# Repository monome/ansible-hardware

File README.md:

# ansible hardware

eurorack module by https://monome.org

created by brian crabtree (bcrabtree@monome.org)

all circuits in eagle. can be imported to kicad.

firmware: https://github.com/monome/ansible

## notes

"ansible" is the top board, "runes" is the bottom board

## license

[cc-by-sa-3.0](https://creativecommons.org/licenses/by-sa/4.0/)

commerical use: send $10 per unit produced to tehn@nnnnnnnn.co via paypal

do not use the name "monome" or "ansible" in derivative works.

## warranty and support

we can provide neither

## thank you

everyone who helped this module live

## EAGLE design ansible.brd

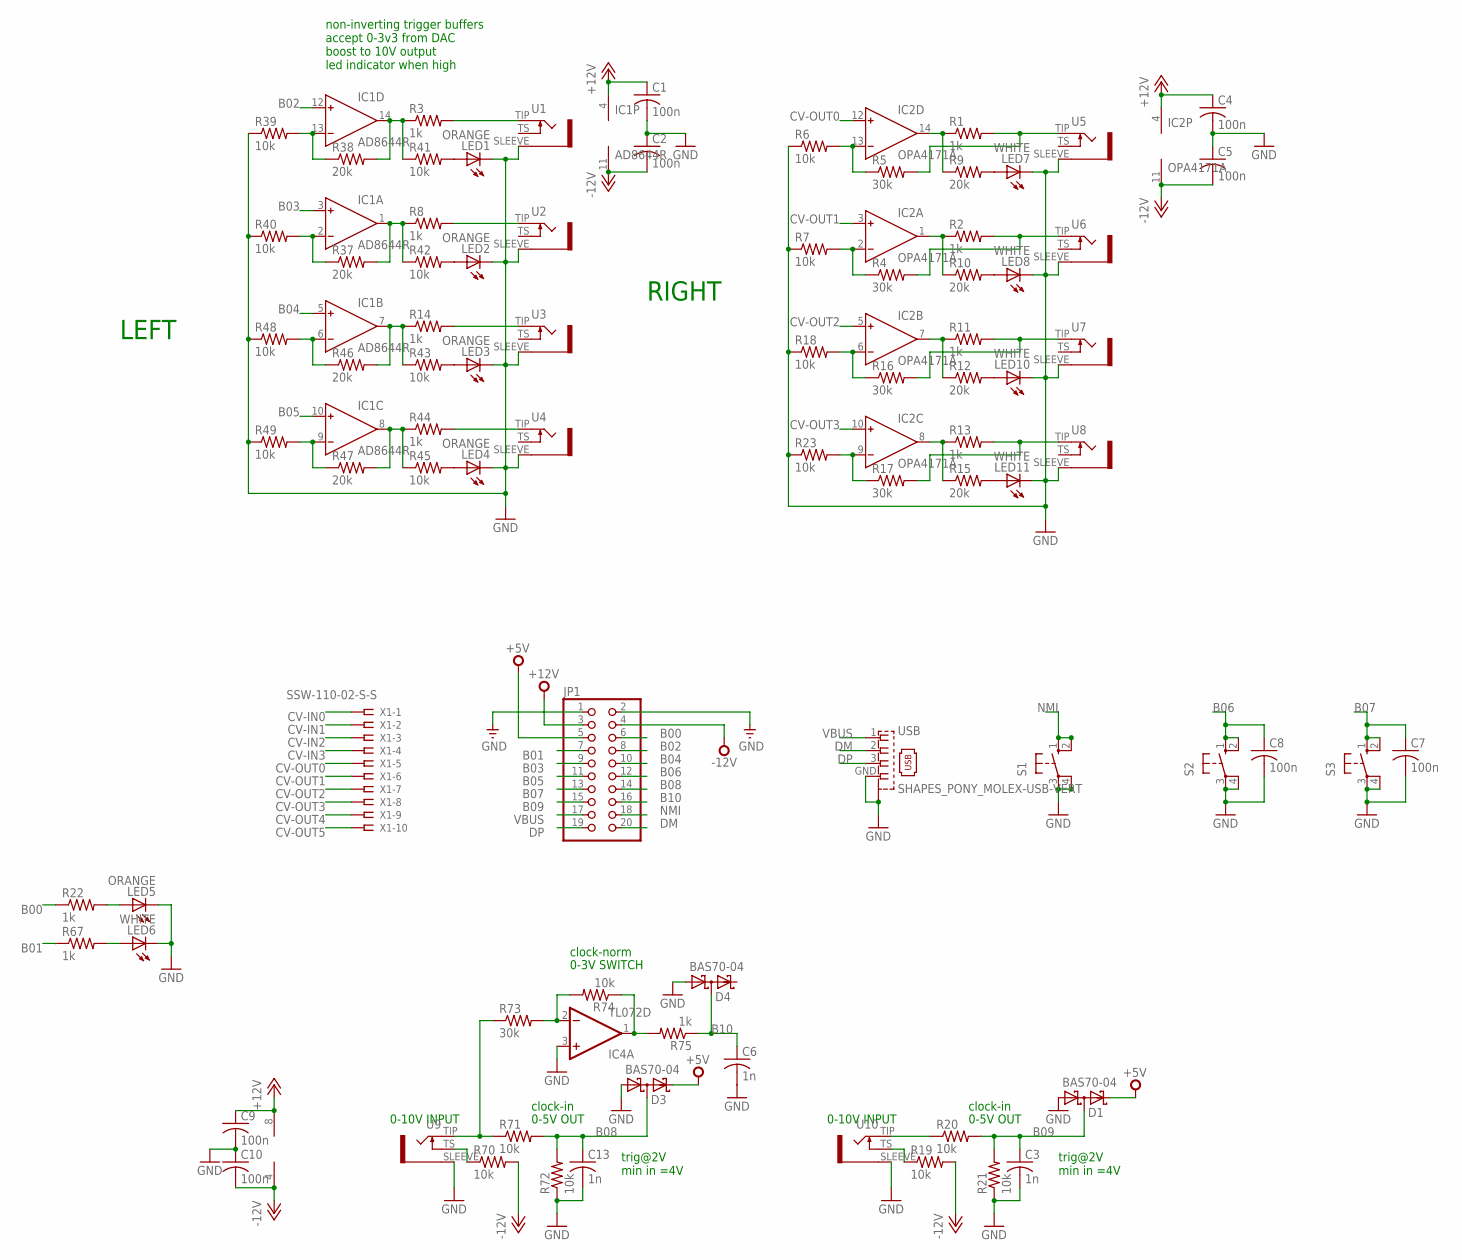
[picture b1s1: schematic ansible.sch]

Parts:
C1, C2, C4, C5, C7, C8, C9, C10: 100n; C0402
C3, C6, C13: 1n; C0402
D1, D3, D4: BAS70-04; SOT23
IC1: AD8644R; SO14
IC2: OPA4171A; SO14
IC4: TL072D; SO08
JP1: PINHD-2X10; 2X10
LED1, LED2, LED3, LED4, LED5: ORANGE; CHIP-LED0603
LED6, LED7, LED8, LED10, LED11: WHITE; CHIP-LED0603
R1, R2, R3, R8, R11, R13, R14, R22, R44, R67, R75: 1k; R0402
R4, R5, R16, R17, R73: 30k; R0402
R6, R7, R18, R19, R20, R21, R23, R39, R40, R41, R42, R43, R45, R48, R49, R70, R71, R72, R74: 10k; R0402
R9, R10, R12, R15, R37, R38, R46, R47: 20k; R0402
S1, S2, S3: 10-XX; B3F-10XX
U1, U2, U3, U4, U5, U6, U7, U8, U9, U10: WQP-PJ301M-12_JACK
USB: SHAPES_PONY_MOLEX-USB-VERT; SHAPES_PONY_MOLEX-USB
X1: SSW-110-02-S-S

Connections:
+5V: D1.2 (C2), D3.2 (C2), JP1.5
+12V: C1.1, C4.1, C9.1, IC1.4 (V+), IC2.4 (V+), IC4.8 (V+), JP1.3
-12V: C2.2, C5.2, C10.2, IC1.11 (V-), IC2.11 (V-), IC4.4 (V-), JP1.4, R19.2, R70.2
B00: JP1.6, R22.1
B01: JP1.7, R67.1
B02: IC1.12 (IN+), JP1.8
B03: IC1.3 (IN+), JP1.9
B04: IC1.5 (IN+), JP1.10
B05: IC1.10 (IN+), JP1.11
B06: C8.1, JP1.12, S2.1 (S), S2.2 (S1)
B07: C7.1, JP1.13, S3.1 (S), S3.2 (S1)
B08: C13.1, D3.3 (C1A2), JP1.14, R71.2, R72.2
B09: C3.1, D1.3 (C1A2), JP1.15, R20.2, R21.2
B10: C6.1, D4.3 (C1A2), JP1.16, R75.1
CV-IN0: X1.1
CV-IN1: X1.2
CV-IN2: X1.3
CV-IN3: X1.4
CV-OUT0: IC2.12 (IN+), X1.5
CV-OUT1: IC2.3 (IN+), X1.6
CV-OUT2: IC2.5 (IN+), X1.7
CV-OUT3: IC2.10 (IN+), X1.8
CV-OUT4: X1.9
CV-OUT5: X1.10
DM: JP1.20, USB.2
DP: JP1.19, USB.3
GND: C1.2, C2.1, C3.2, C4.2, C5.1, C6.2, C7.2, C8.2, C9.2, C10.1, C13.2, D1.1 (A1), D3.1 (A1), D4.1 (A1), IC4.3 (+IN), JP1.1, JP1.2, LED1.C, LED2.C, LED3.C, LED4.C, LED5.C, LED6.C, LED7.C, LED8.C, LED10.C, LED11.C, R6.1, R7.1, R18.1, R21.1, R23.1, R39.1, R40.1, R48.1, R49.1, R72.1, S1.3, S1.4 (P1), S2.3, S2.4 (P1), S3.3, S3.4 (P1), U1.SLEEVE, U2.SLEEVE, U3.SLEEVE, U4.SLEEVE, U5.SLEEVE, U6.SLEEVE, U7.SLEEVE, U8.SLEEVE, U9.SLEEVE, U10.SLEEVE, USB.GND, USB.M1 (S1), USB.M2 (S1), USB.M4 (S1)
N: IC4.1 (OUT), R74.1, R75.2
unnamed: IC4.2 (-IN), R73.2, R74.2
unnamed: IC1.14 (OUT), R3.1, R38.2, R41.1
unnamed: IC1.1 (OUT), R8.1, R37.2, R42.1
unnamed: IC1.7 (OUT), R14.1, R43.1, R46.2
unnamed: IC1.8 (OUT), R44.1, R45.1, R47.2
unnamed: R3.2, U1.TIP
unnamed: R8.2, U2.TIP
unnamed: R14.2, U3.TIP
unnamed: R44.2, U4.TIP
unnamed: R20.1, U10.TIP
unnamed: IC2.14 (OUT), R1.1, R9.1
unnamed: IC2.1 (OUT), R2.1, R10.1
unnamed: IC2.7 (OUT), R11.1, R12.1
unnamed: IC2.8 (OUT), R13.1, R15.1
unnamed: LED5.A, R22.2
unnamed: R13.2, R17.2, U8.TIP
unnamed: IC2.13 (IN-), R5.1, R6.2
unnamed: IC2.2 (IN-), R4.1, R7.2
unnamed: LED7.A, R9.2
unnamed: LED8.A, R10.2
unnamed: R70.1, U9.TS
unnamed: R19.1, U10.TS
unnamed: IC2.9 (IN-), R17.1, R23.2
unnamed: IC2.6 (IN-), R16.1, R18.2
unnamed: LED10.A, R12.2
unnamed: LED11.A, R15.2
unnamed: R1.2, R5.2, U5.TIP
unnamed: R2.2, R4.2, U6.TIP
unnamed: R11.2, R16.2, U7.TIP
unnamed: IC1.9 (IN-), R47.1, R49.2
unnamed: IC1.6 (IN-), R46.1, R48.2
unnamed: R71.1, R73.1, U9.TIP
unnamed: IC1.13 (IN-), R38.1, R39.2
unnamed: IC1.2 (IN-), R37.1, R40.2
unnamed: LED6.A, R67.2
unnamed: LED1.A, R41.2
unnamed: LED2.A, R42.2
unnamed: LED3.A, R43.2
unnamed: LED4.A, R45.2
NMI: JP1.18, S1.1 (S), S1.2 (S1)
VBUS: JP1.17, USB.1

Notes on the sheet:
0-10V INPUT
0-5V OUT
0-3V SWITCH
non-inverting trigger buffers accept 0-3v3 from DAC boost to 10V output led indicator when high
LEFT
RIGHT
clock-norm
clock-in
trig@2V min in =4V

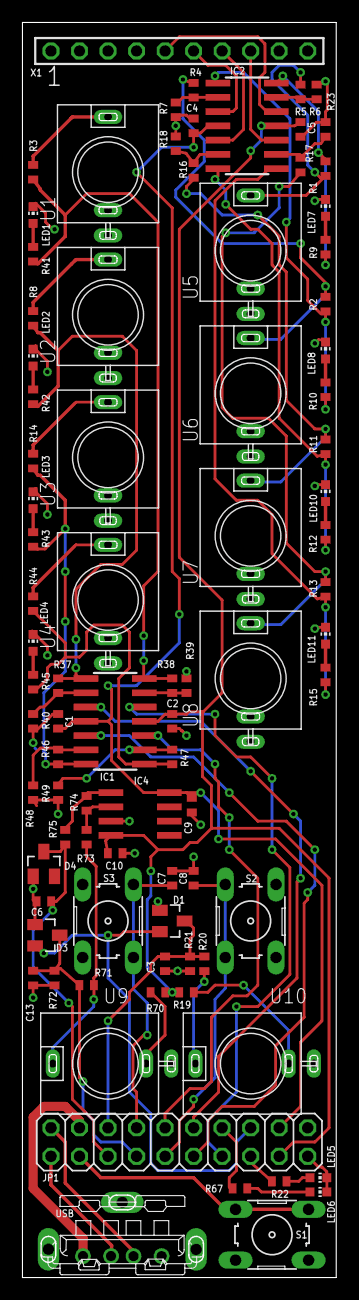
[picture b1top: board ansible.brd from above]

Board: 2 copper layers, 27.9 x 111.8 mm, 86 parts (0 on the bottom side), 63 nets.

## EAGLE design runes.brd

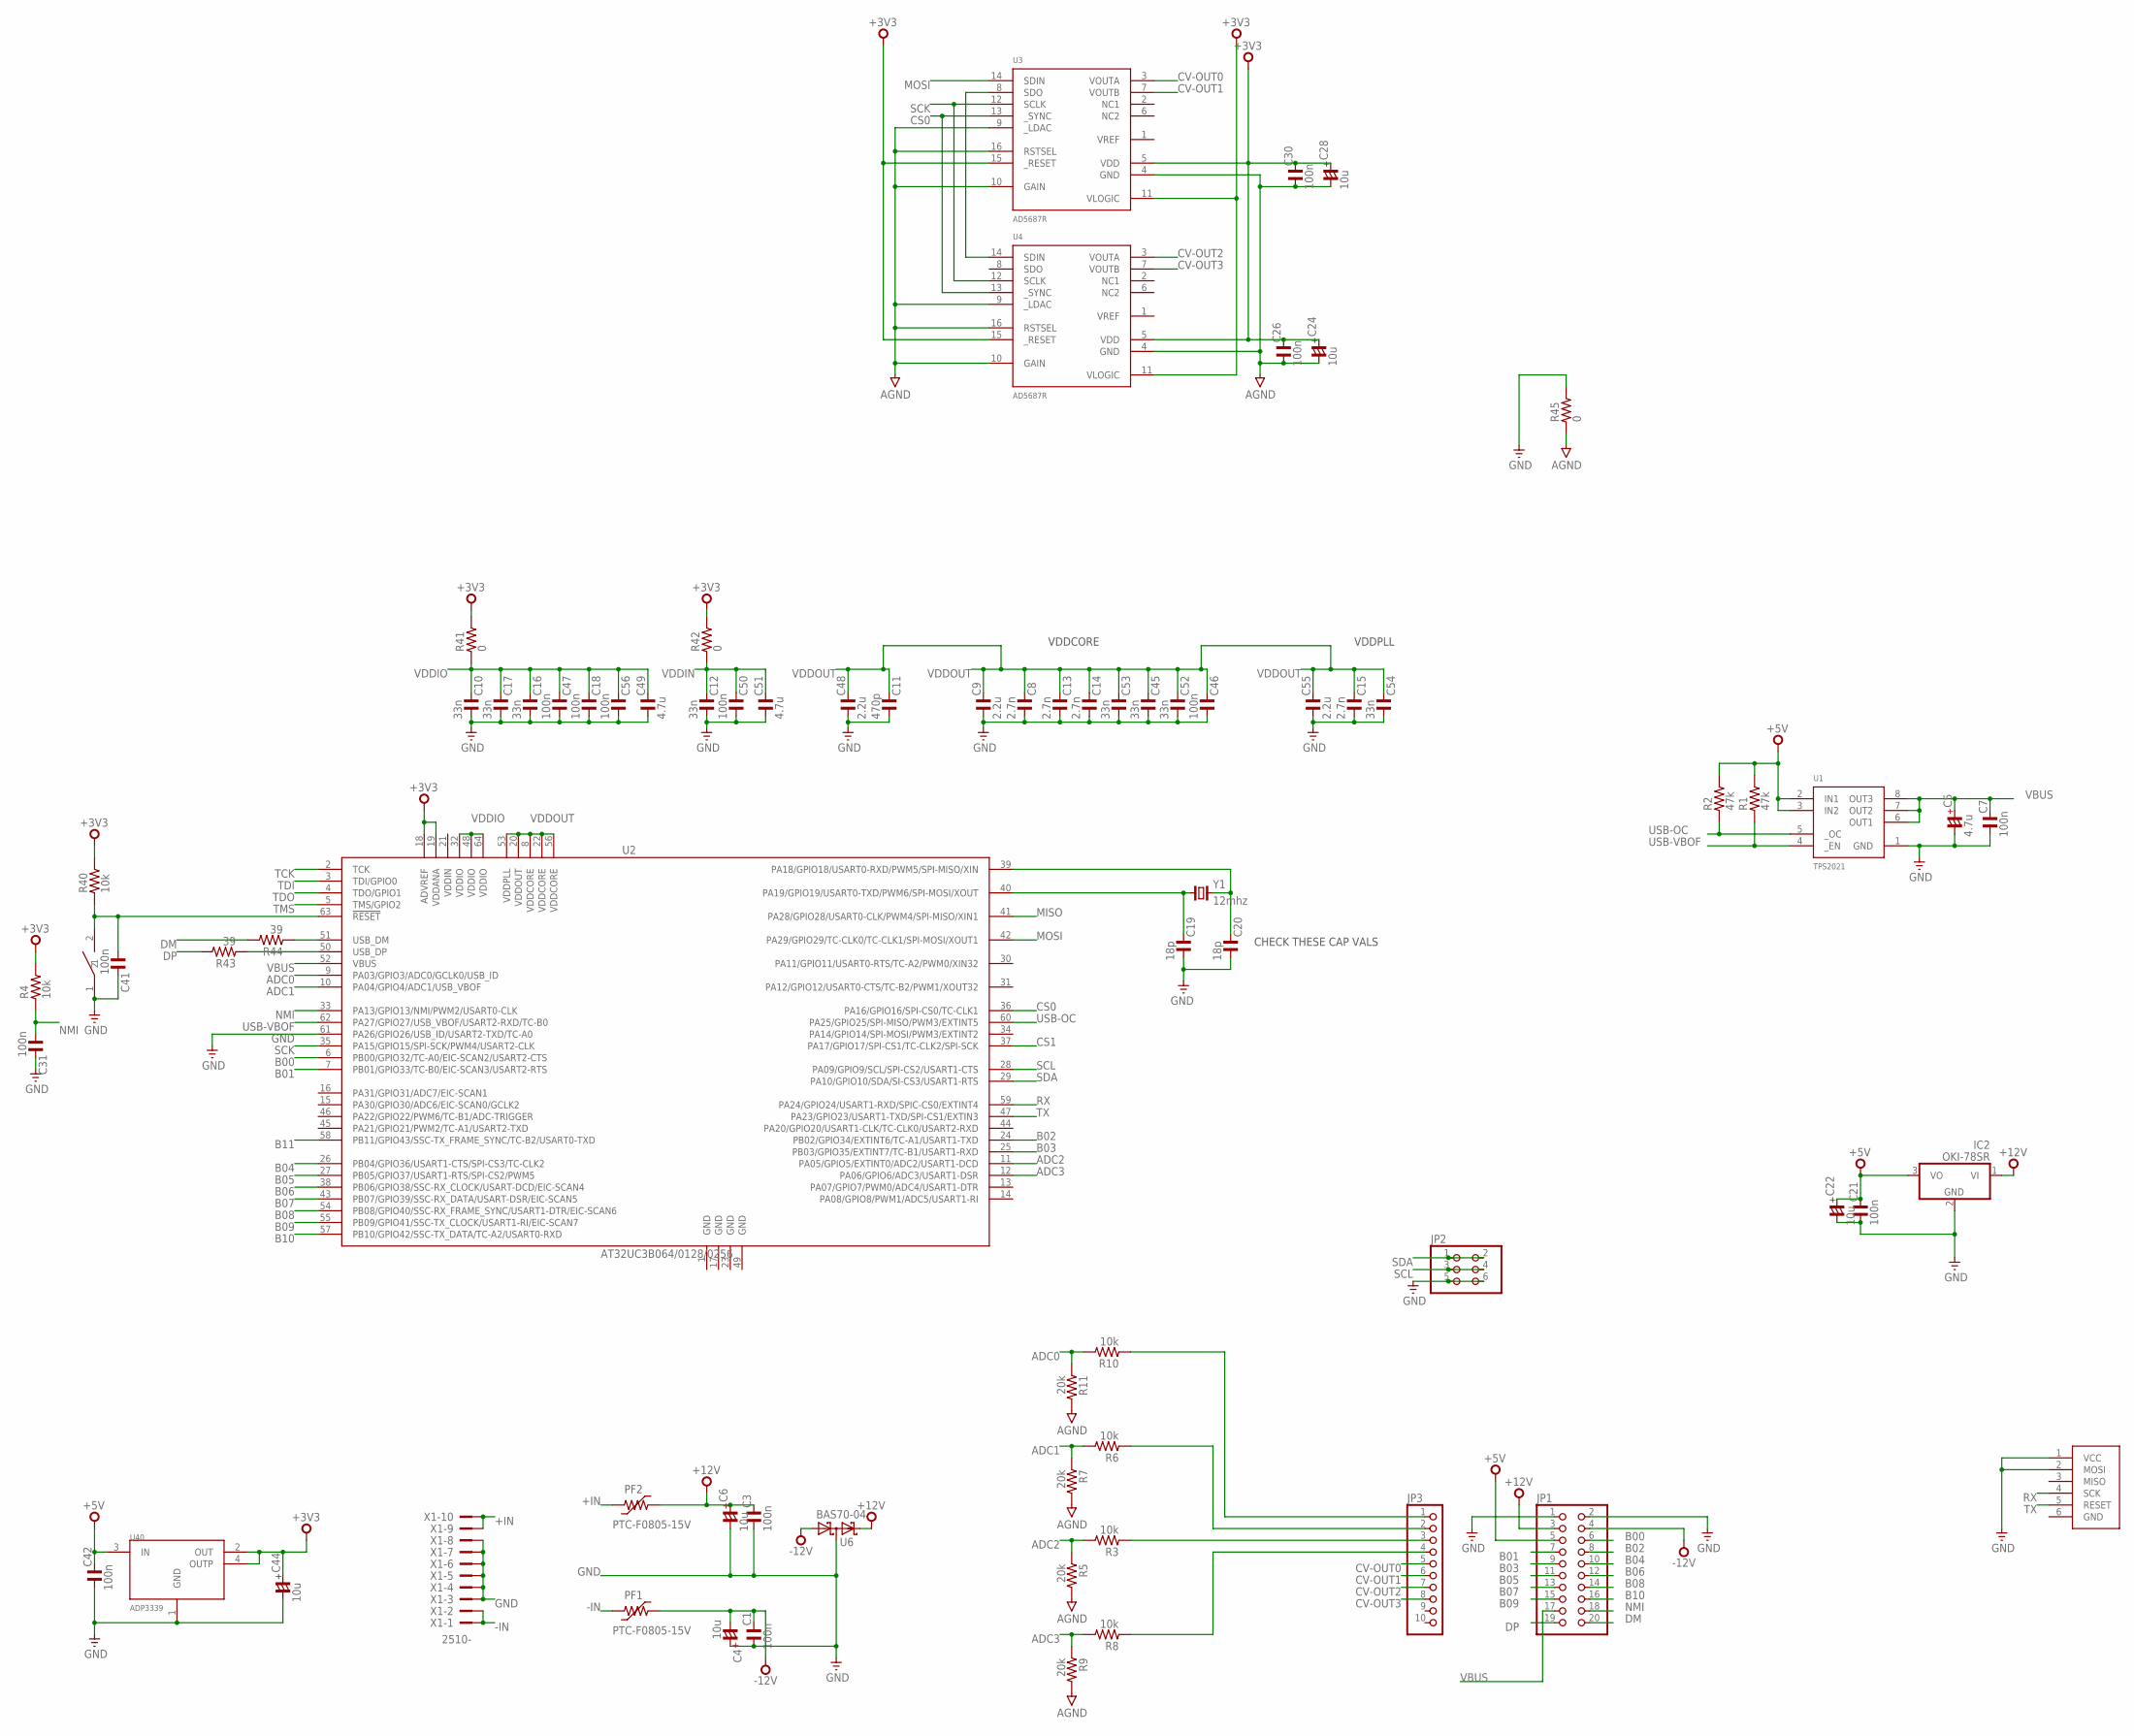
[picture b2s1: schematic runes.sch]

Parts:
C1, C3, C7, C18, C21, C26, C30, C31, C41, C42, C46, C47, C50, C56: 100n; C0402
C4, C6, C22, C24, C28, C44: 10u; C1206/T
C5: 4.7u; C1206/T
C8, C13, C14, C15: 2.7n; C0402
C9, C48, C55: 2.2u; C0603
C10, C12, C16, C17, C45, C52, C53, C54: 33n; C0402
C11: 470p; C0402
C19, C20: 18p; C0402
C49, C51: 4.7u; C0603
IC2: OKI-78SR; TO220V
J40: ISP-ROW
JP1: PINHD-2X10; 2X10
JP2: PINHD-2X3; 2X03
JP3: PINHD-1X10; 1X10
PF1, PF2: PTC-F0805-15V; F0805
R1, R2: 47k; R0402
R3, R4, R6, R8, R10, R40: 10k; R0402
R5, R7, R9, R11: 20k; R0402
R41, R42, R45: 0; R0402
R43, R44: 39; R0402
SW40: PANASONIC-EVQ
U1: TPS2021; SO08
U2: AT32UC3B064/0128/0256; TQFP64-10X10
U3, U4: AD5687R; TSSOP16
U6: BAS70-04; SOT23
U40: ADP3339; SOT223
X1: 2510-; PAK100/2500-10
Y1: 12mhz; HC49UP

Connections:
+3V3: C24.+, C26.2, C28.+, C30.2, C44.+, R4.2, R40.2, R41.2, R42.2, U2.18 (ADVREF), U2.19 (VDDANA), U3.5 (VDD), U3.11 (VLOGIC), U3.15 (_RESET), U4.5 (VDD), U4.11 (VLOGIC), U4.15 (_RESET), U40.2 (OUT), U40.4 (OUTP)
+5V: C21.2, C22.+, C42.2, IC2.3 (VO), JP1.5, R1.2, R2.2, U1.2 (IN1), U1.3 (IN2), U40.3 (IN)
+12V: C3.2, C6.+, IC2.1 (VI), JP1.3, PF2.2, U6.2 (C2)
+IN: PF2.1, X1.9, X1.10
-12V: C1.2, C4.-, JP1.4, PF1.2, U6.1 (A1)
-IN: PF1.1, X1.1, X1.2
ADC0: R10.2, R11.1, U2.9 (PA03/GPIO3/ADC0/GCLK0/USB_ID)
ADC1: R6.2, R7.1, U2.10 (PA04/GPIO4/ADC1/USB_VBOF)
ADC2: R3.2, R5.1, U2.11 (PA05/GPIO5/EXTINT0/ADC2/USART1-DCD)
ADC3: R8.2, R9.1, U2.12 (PA06/GPIO6/ADC3/USART1-DSR)
AGND: C24.-, C26.1, C28.-, C30.1, R5.2, R7.2, R9.2, R11.2, R45.1, U3.4 (GND), U3.9 (_LDAC), U3.10 (GAIN), U3.16 (RSTSEL), U4.4 (GND), U4.9 (_LDAC), U4.10 (GAIN), U4.16 (RSTSEL)
B00: JP1.6, U2.6 (PB00/GPIO32/TC-A0/EIC-SCAN2/USART2-CTS)
B01: JP1.7, U2.7 (PB01/GPIO33/TC-B0/EIC-SCAN3/USART2-RTS)
B02: JP1.8, U2.24 (PB02/GPIO34/EXTINT6/TC-A1/USART1-TXD)
B03: JP1.9, U2.25 (PB03/GPIO35/EXTINT7/TC-B1/USART1-RXD)
B04: JP1.10, U2.26 (PB04/GPIO36/USART1-CTS/SPI-CS3/TC-CLK2)
B05: JP1.11, U2.27 (PB05/GPIO37/USART1-RTS/SPI-CS2/PWM5)
B06: JP1.12, U2.38 (PB06/GPIO38/SSC-RX_CLOCK/USART-DCD/EIC-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)
B07: JP1.13, U2.43 (PB07/GPIO39/SSC-RX_DATA/USART-DSR/EIC-S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)
B08: JP1.14, U2.54 (PB08/GPIO40/SSC-RX_FRAME_SYNC/USART1-DT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)
B09: JP1.15, U2.55 (PB09/GPIO41/SSC-TX_CLOCK/USART1-RI/EIC-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)
B10: JP1.16, U2.57 (PB10/GPIO42/SSC-TX_DATA/TC-A2/USART0-RXD)
B11: U2.58 (PB11/GPIO43/SSC-TX_FRAME_SYNC/TC-B2/USA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)
CS0: U2.36 (PA16/GPIO16/SPI-CS0/TC-CLK1), U3.13 (_SYNC), U4.13 (_SYNC)
CS1: U2.37 (PA17/GPIO17/SPI-CS1/TC-CLK2/SPI-SCK)
CV-OUT0: JP3.5, U3.3 (VOUTA)
CV-OUT1: JP3.6, U3.7 (VOUTB)
CV-OUT2: JP3.7, U4.3 (VOUTA)
CV-OUT3: JP3.8, U4.7 (VOUTB)
DM: JP1.20, R44.2
DP: JP1.19, R43.2
GND: C1.1, C3.1, C4.+, C5.-, C6.-, C7.1, C8.1, C9.1, C10.1, C11.1, C12.1, C13.1, C14.1, C15.1, C16.1, C17.1, C18.1, C19.1, C20.1, C21.1, C22.-, C31.2, C41.2, C42.1, C44.-, C45.1, C46.1, C47.1, C48.1, C49.1, C50.1, C51.1, C52.1, C53.1, C54.1, C55.1, C56.1, IC2.2 (GND), J40.1 (VCC), J40.2 (MOSI), JP1.1, JP1.2, JP2.5, JP2.6, R45.2, SW40.1, U1.1 (GND), U2.1 (GND), U2.17 (GND), U2.23 (GND), U2.49 (GND), U2.61 (PA26/GPIO26/USB_ID/USART2-TXD/TC-A0), U6.3 (C1A2), U40.1 (GND), X1.3, X1.4, X1.5, X1.6, X1.7, X1.8
MISO: U2.41 (PA28/GPIO28/USART0-CLK/PWM4/SPI-MISO/XI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)
MOSI: U2.42 (PA29/GPIO29/TC-CLK0/TC-CLK1/SPI-MOSI/XO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), U3.14 (SDIN)
unnamed: R44.1, U2.51 (USB_DM)
unnamed: R43.1, U2.50 (USB_DP)
unnamed: JP3.1, R10.1
unnamed: U3.8 (SDO), U4.14 (SDIN)
unnamed: JP3.2, R6.1
unnamed: JP3.3, R3.1
unnamed: JP3.4, R8.1
unnamed: C20.2, U2.39 (PA18/GPIO18/USART0-RXD/PWM5/SPI-MISO/XIN), Y1.2
unnamed: C19.2, U2.40 (PA19/GPIO19/USART0-TXD/PWM6/SPI-MOSI/XO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), Y1.1
NMI: C31.1, JP1.18, R4.1, U2.33 (PA13/GPIO13/NMI/PWM2/USART0-CLK)
RESET: C41.1, R40.1, SW40.2, U2.63 (!RESET)
RX: J40.4 (SCK), U2.59 (PA24/GPIO24/USART1-RXD/SPIC-CS0/EXTINT4)
SCK: U2.35 (PA15/GPIO15/SPI-SCK/PWM4/USART2-CLK), U3.12 (SCLK), U4.12 (SCLK)
SCL: JP2.3, JP2.4, U2.28 (PA09/GPIO9/SCL/SPI-CS2/USART1-CTS)
SDA: JP2.1, JP2.2, U2.29 (PA10/GPIO10/SDA/SI-CS3/USART1-RTS)
TCK: U2.2 (TCK)
TDI: U2.3 (TDI/GPIO0)
TDO: U2.4 (TDO/GPIO1)
TMS: U2.5 (TMS/GPIO2)
TX: J40.5 (RESET), U2.47 (PA23/GPIO23/USART1-TXD/SPI-CS1/EXTIN3)
USB-OC: R2.1, U1.5 (_OC), U2.60 (PA25/GPIO25/SPI-MISO/PWM3/EXTINT5)
USB-VBOF: R1.1, U1.4 (_EN), U2.62 (PA27/GPIO27/USB_VBOF/USART2-RXD/TC-B0)
VBUS: C5.+, C7.2, JP1.17, U1.6 (OUT1), U1.7 (OUT2), U1.8 (OUT3), U2.52 (VBUS)
VDDIN: C12.2, C50.2, C51.2, R42.1, U2.21 (VDDIN)
VDDIO: C10.2, C16.2, C17.2, C18.2, C47.2, C49.2, C56.2, R41.1, U2.32 (VDDIO), U2.48 (VDDIO), U2.64 (VDDIO)
VDDOUT: C8.2, C9.2, C11.2, C13.2, C14.2, C15.2, C45.2, C46.2, C48.2, C52.2, C53.2, C54.2, C55.2, U2.8 (VDDCORE), U2.20 (VDDOUT), U2.22 (VDDCORE), U2.53 (VDDPLL), U2.56 (VDDCORE)

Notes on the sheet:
CHECK THESE CAP VALS
VDDCORE
VDDPLL

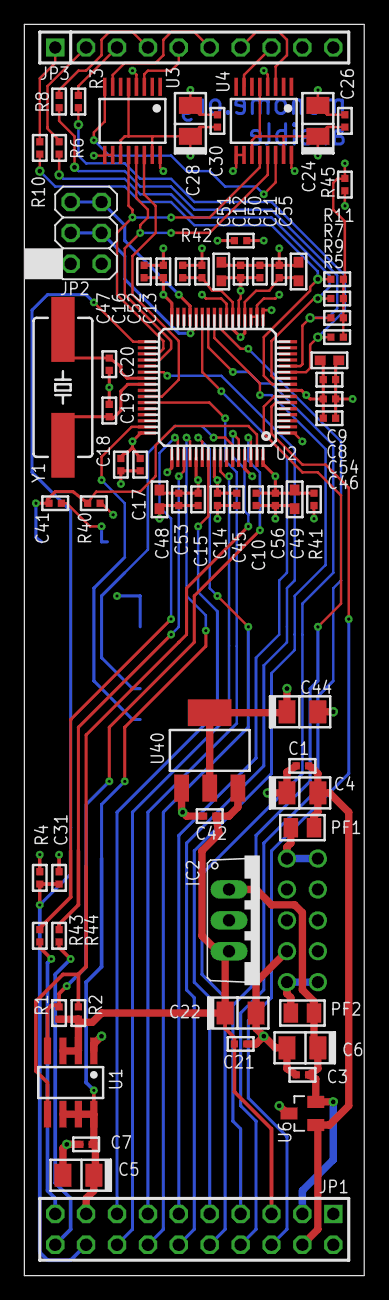
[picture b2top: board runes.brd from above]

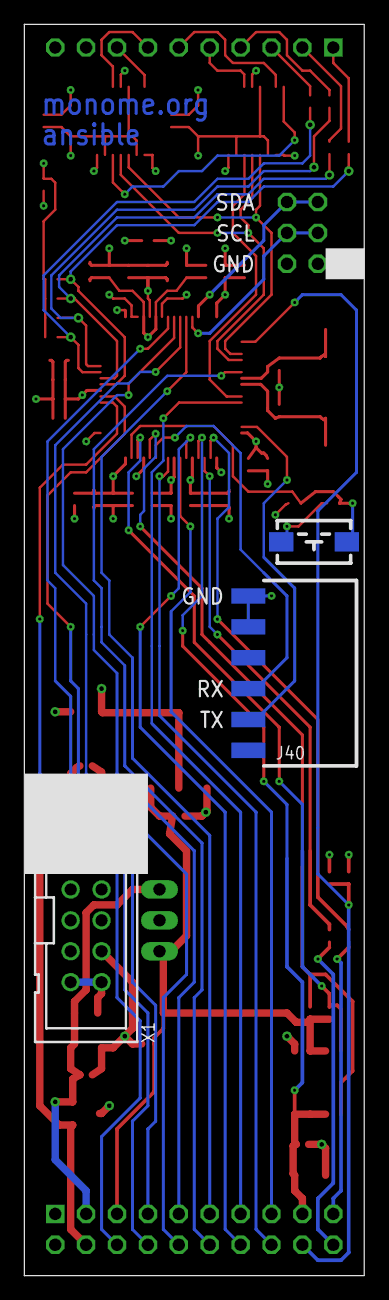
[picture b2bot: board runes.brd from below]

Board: 4 copper layers, 27.9 x 102.9 mm, 74 parts (3 on the bottom side), 53 nets.

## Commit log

2026-05-24 first
2026-05-24 readme

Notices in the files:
parts and their libraries:
atmel-avr32-michel-rev1: Copyright (C) 2010 Michel Catudal mcatudal@comcast.net
polyswitch: Copyright (C) 2008, Bob Starr
